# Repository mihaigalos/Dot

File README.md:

# Dot

The Dot is a carrier board designed in Eagle, aimed at gathering sensor data from a variety of sensors and sending them over radio.
Its small design and supply from a coin cell battery make it ideal for deployment anywhere.

Features :
* AtMega328p MCU
* RFM12b / RFM69CW Radio module (pin-compatible)
* On-board ceramic antenna
* CAT24M010TS EEPROM (128kByte)
* AT25SF081 Flash (1MByte)
* Breakout of I2C, SPI and UART-TXD
* Breakout of ADC Pin with pads for on-board divider resistor
* Antenna tuning pads for antenna calibration
* uFL connector for external antenna support 
* Sensors
  * MPU-9250 Movement sensor (9DoF : accelerometers, gyros and magnetometer)
  * TMP102 Temperature and Humidity
  * SI1145 UV Index
  * ISL29125 RGB color
  * Analog light sensor

# License
The Dot is Open Hardware. Use it at your own whim and risk, please share if you find it useful.

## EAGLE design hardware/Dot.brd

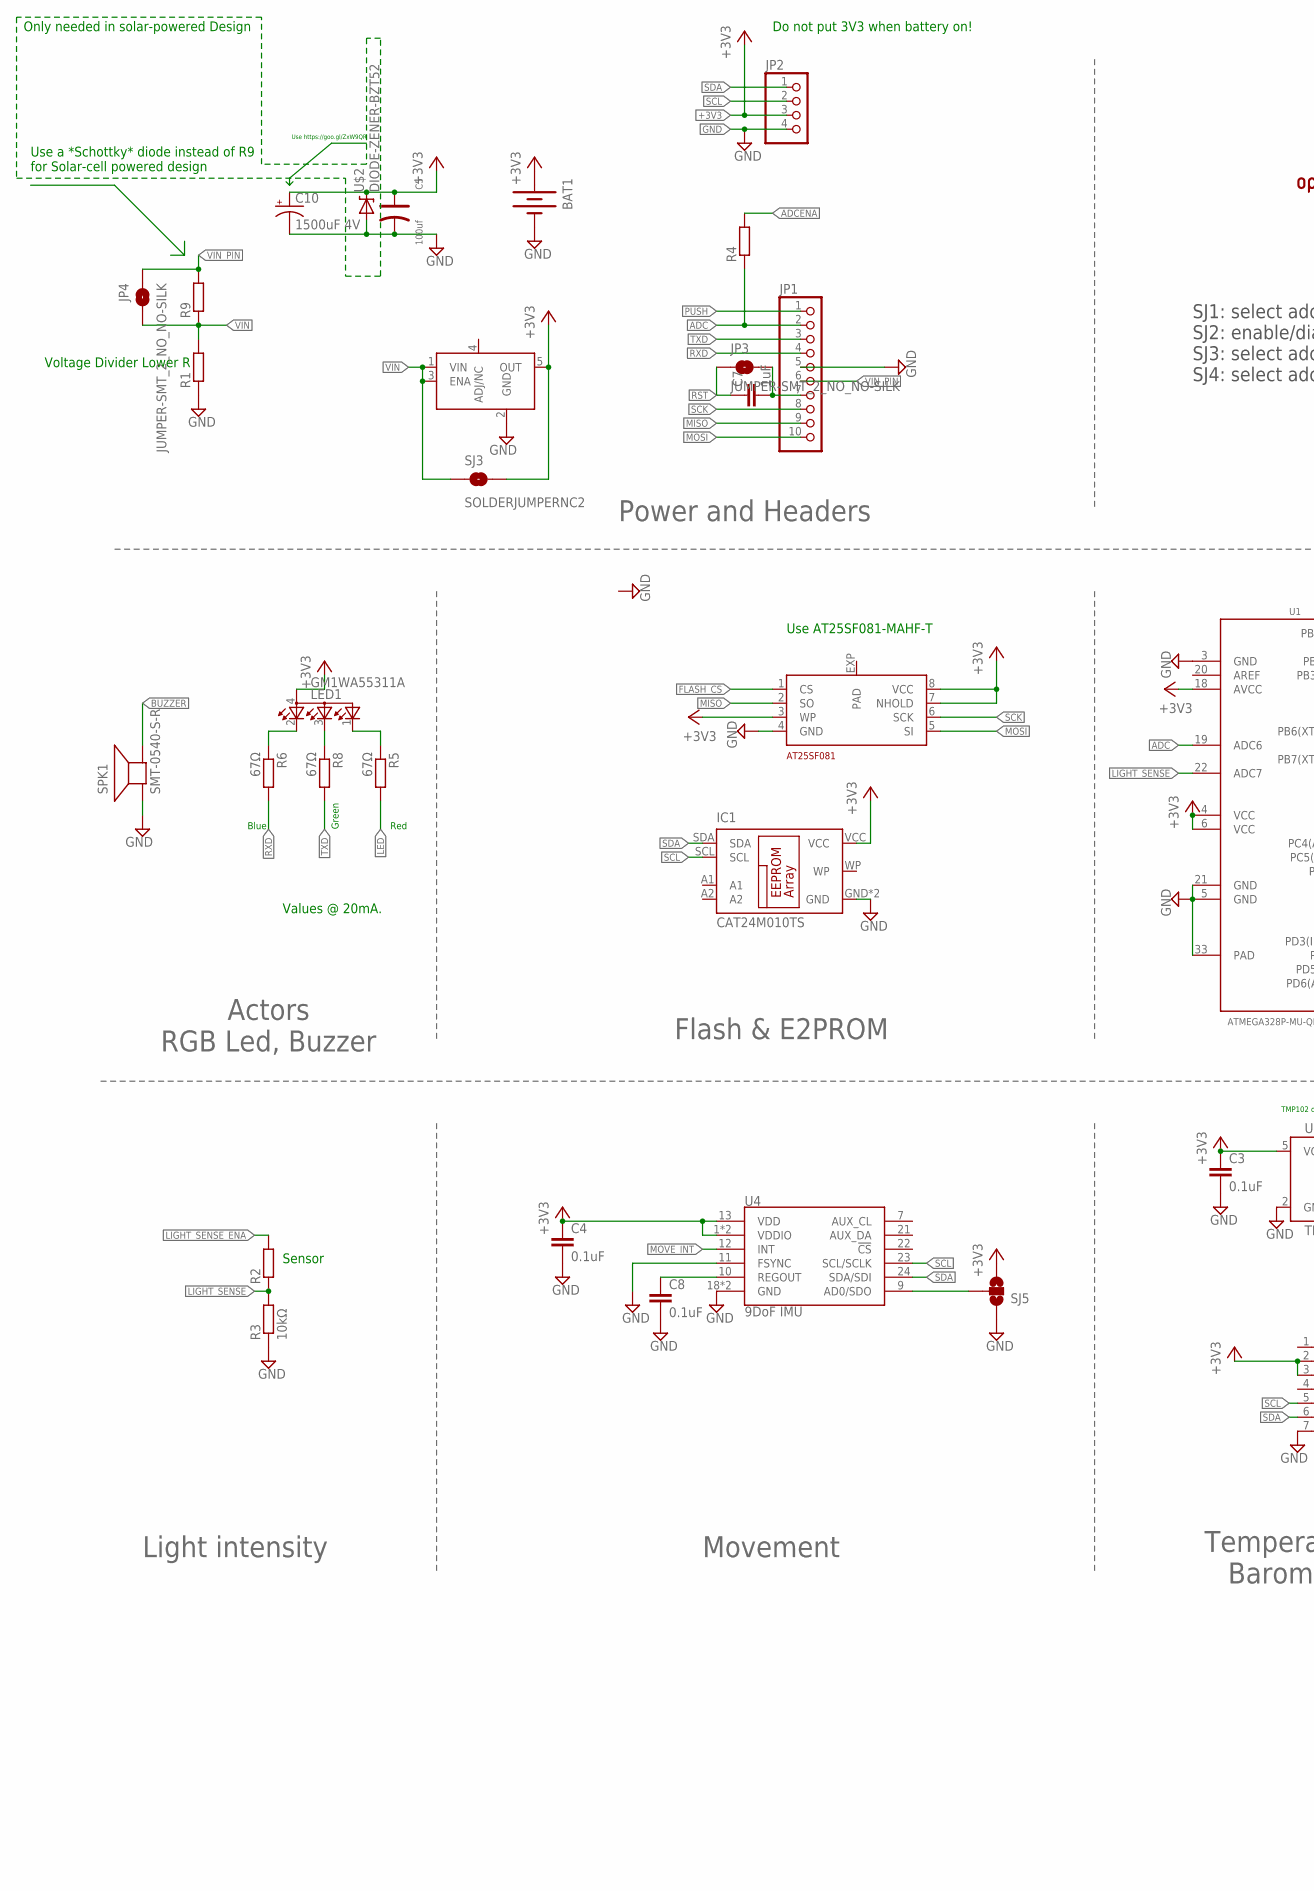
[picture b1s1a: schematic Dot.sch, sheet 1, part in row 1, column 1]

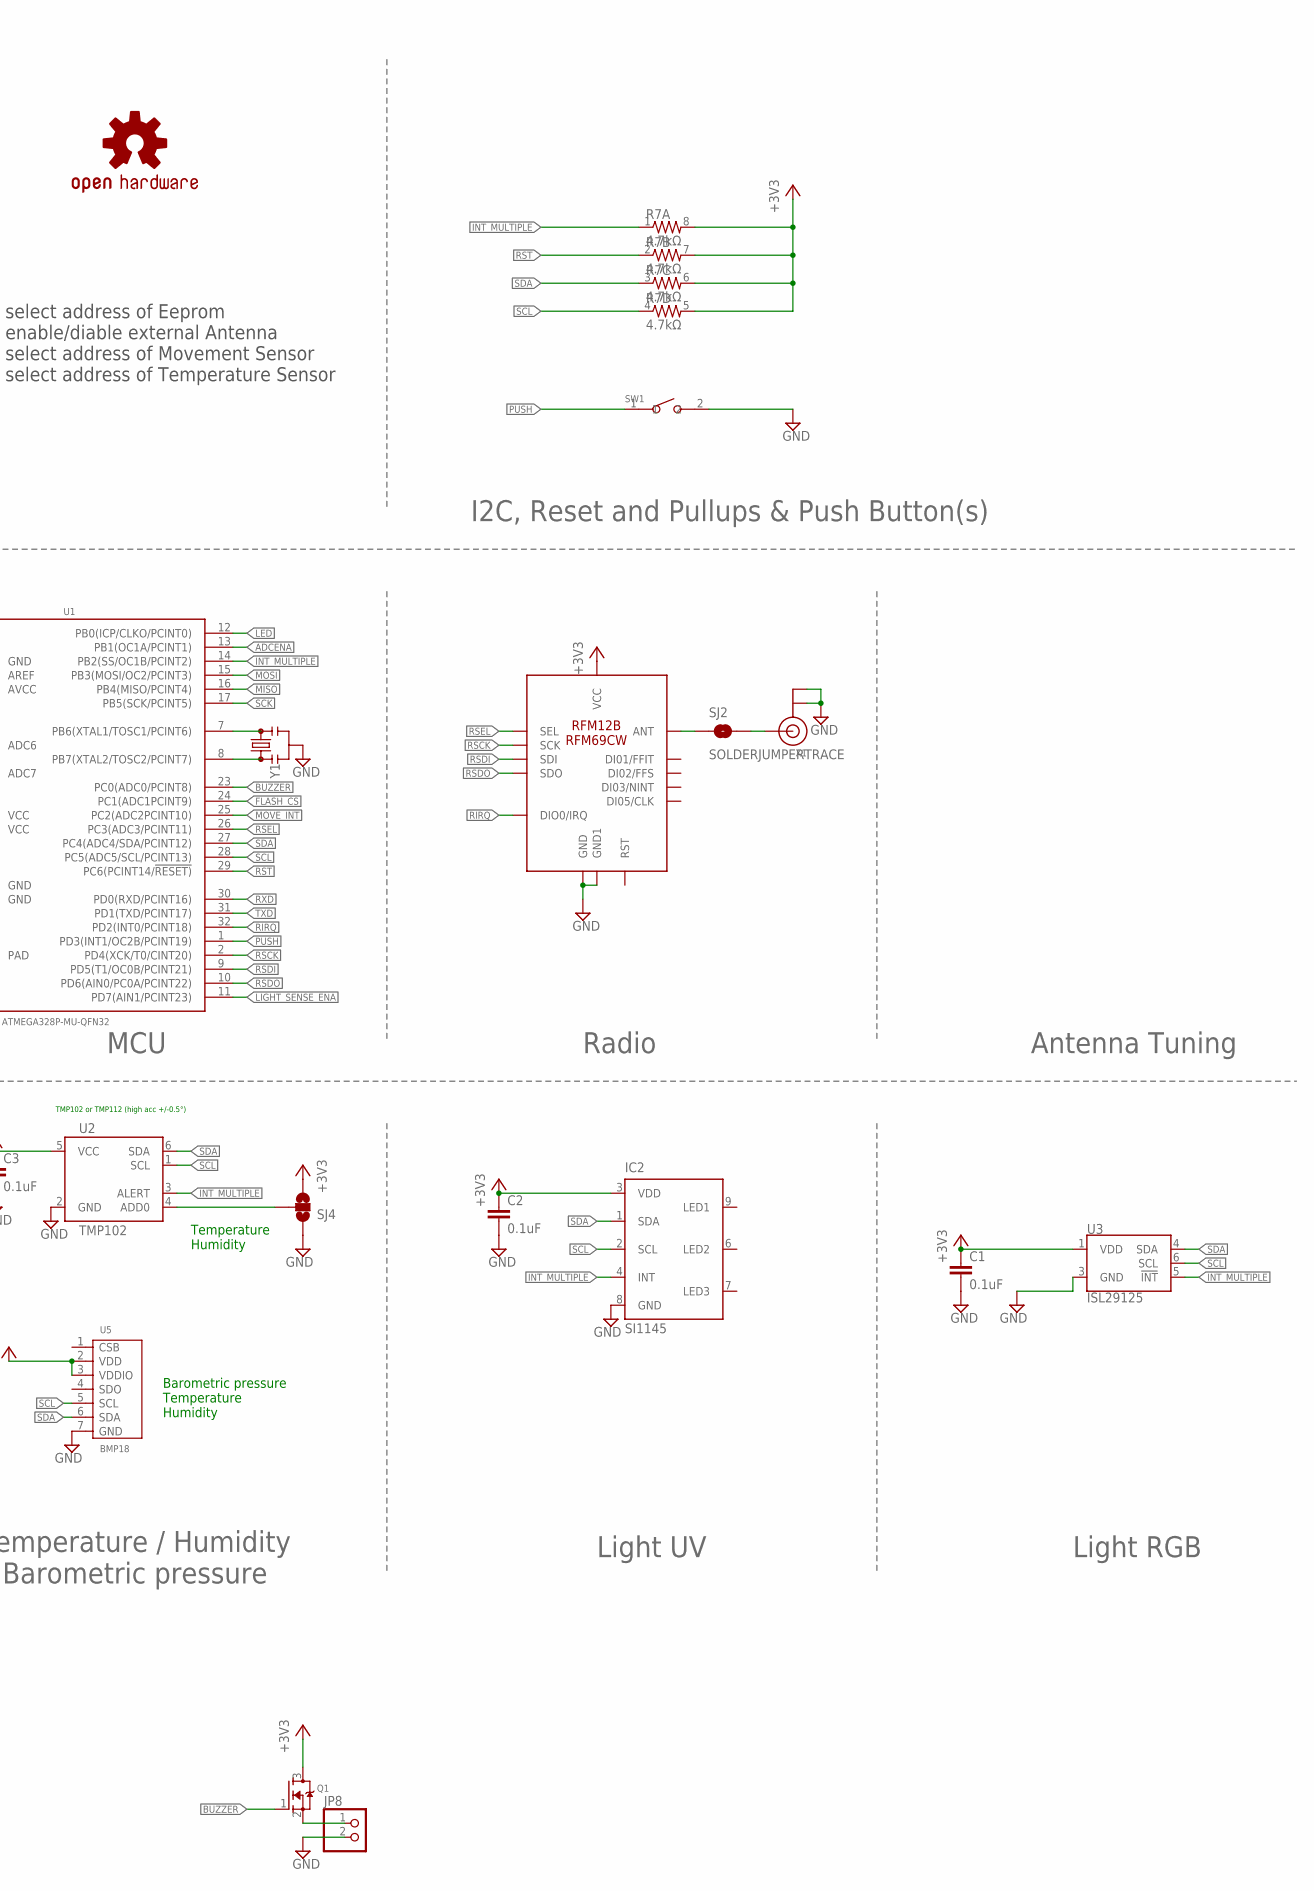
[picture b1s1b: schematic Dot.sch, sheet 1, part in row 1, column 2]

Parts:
BAT1: BATTERY20PTH; BATTCOM_20MM_PTH
C1, C2, C3, C4, C8: 0.1uF; C0603
C5: 100uf; AVX-A
C7: 1uF; C0603
C10: 1500uF 4V; CT7343
IC1: CAT24M010TS; TSSOP8
IC2: SI1145; QFN-10
JP1: PINHD-1X10; 1X10
JP2: PINHD-1X4; 1X04
JP3, JP4: JUMPER-SMT_2_NO_NO-SILK; SMT-JUMPER_2_NO_NO-SILK
JP8: PINHD-1X2; 1X02
LED1: GM1WA55311A
LOGO1: OSHW-LOGOS; OSHW-LOGO-S
Q1: MOSFET-NREFLOW; SOT23
R1, R4, R9: R-EU_R0603; R0603
R2: R-EU_R0805; R0805
R3: 10kΩ; R0603
R5, R6, R8: 67Ω; R0603
R7: 4.7kΩ; 0603-ARV
SJ2: SOLDERJUMPERTRACE; SJ_2S-TRACE
SJ3: SOLDERJUMPERNC2; SJ_2S-NOTRACE
SJ4, SJ5: SOLDERJUMPER_2WAYS; SJ_3
SPK1: SMT-0540-S-R
SW1: SMD-BUTTON(2P-6.0X3.0X2.5MM)-DHT-1163S; SW2-4.0-6.0X3.0X2.5MM
U1: ATMEGA328P-MU-QFN32; QFN32G-0.5-5X5MM
U2: TMP102; SOT563
U3: ISL29125; ODFN-6
U4: 9DoF IMU; QFN24-3X3
U5: BMP18; LGA7-1.5-3.8X3.6MM
U$1: RFM12B/69CW
U$2: DIODE-ZENER-BZT52; SOD-323
U$3: AT25SF081; DFN-2X3
U$4: LDCL015; SOT23-5
X1: ANTENNA_U.FL; U.FL
Y1: RESONATORSMD-3.2X1.3; RESONATOR-SMD-3.2X1.3

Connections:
+3V3: BAT1.1 (+), C1.1, C2.1, C3.1, C4.1, C5.+, C10.+, IC1.VCC, IC2.3 (VDD), JP2.3, LED1.4 (A), Q1.3 (D), R7.5 (2), R7.6 (2), R7.7 (2), R7.8 (2), SJ3.2, SJ4.3, SJ5.3, U1.4 (VCC), U1.6 (VCC), U1.18 (AVCC), U2.5 (VCC), U3.1 (VDD), U4.1 (VDDIO), U4.8 (VDDIO), U4.13 (VDD), U5.2 (VDD), U5.3 (VDDIO), U$1.VDD (VCC), U$2.1 (C), U$3.3 (WP), U$3.7 (NHOLD), U$3.8 (VCC), U$4.5 (OUT)
ADC: JP1.2, R4.1, U1.19 (ADC6)
ADCENA: R4.2, U1.13 (PB1(OC1A/PCINT1))
BUZZER: Q1.1 (G), SPK1.+ (-), U1.23 (PC0(ADC0/PCINT8))
FLASH_CS: U1.24 (PC1(ADC1PCINT9)), U$3.1 (CS)
GND: BAT1.2 (-), C1.2, C2.2, C3.2, C4.2, C5.-, C8.2, C10.-, IC1.GND, IC1.NC (GND), IC2.8 (GND), JP1.5, JP2.4, JP8.2, R1.1, R3.1, SJ4.1, SJ5.1, SPK1.- (+), SW1.2, U1.3 (GND), U1.5 (GND), U1.21 (GND), U1.33 (PAD), U2.2 (GND), U3.3 (GND), U4.11 (FSYNC), U4.18 (GND), U4.20 (GND), U5.7 (GND), U$1.GND, U$1.GND1, U$2.2 (A), U$3.4 (GND), U$4.2 (GND), X1.1 (GND), X1.2 (GND), Y1.2
INT_MULTIPLE: IC2.4 (INT), R7.1, U1.14 (PB2(SS/OC1B/PCINT2)), U2.3 (ALERT), U3.5 (!INT)
LED: R5.2, U1.12 (PB0(ICP/CLKO/PCINT0))
LIGHT_SENSE: R2.1, R3.2, U1.22 (ADC7)
LIGHT_SENSE_ENA: R2.2, U1.11 (PD7(AIN1/PCINT23))
MISO: JP1.9, U1.16 (PB4(MISO/PCINT4)), U$3.2 (SO)
MOSI: JP1.10, U1.15 (PB3(MOSI/OC2/PCINT3)), U$3.5 (SI)
MOVE_INT: U1.25 (PC2(ADC2PCINT10)), U4.12 (INT)
unnamed: LED1.3 (CBLUE), R8.1
unnamed: SJ2.1, U$1.ANT
unnamed: LED1.2 (CRED), R6.1
unnamed: C7.2, JP1.7, JP3.2
unnamed: U1.7 (PB6(XTAL1/TOSC1/PCINT6)), Y1.3
unnamed: SJ2.2, X1.3 (SIGNAL)
unnamed: U1.8 (PB7(XTAL2/TOSC2/PCINT7)), Y1.1
unnamed: SJ4.2, U2.4 (ADD0)
unnamed: C8.1, U4.10 (REGOUT)
unnamed: SJ5.2, U4.9 (AD0/SDO)
unnamed: LED1.1 (CGREEN), R5.1
unnamed: JP8.1, Q1.2 (S)
PUSH: JP1.1, SW1.1, U1.1 (PD3(INT1/OC2B/PCINT19))
RIRQ: U1.32 (PD2(INT0/PCINT18)), U$1.IRQ (DIO0/IRQ)
RSCK: U1.2 (PD4(XCK/T0/CINT20)), U$1.SCK
RSDI: U1.9 (PD5(T1/OC0B/PCINT21)), U$1.SDI
RSDO: U1.10 (PD6(AIN0/PC0A/PCINT22)), U$1.SDO
RSEL: U1.26 (PC3(ADC3/PCINT11)), U$1.SEL
RST: C7.1, JP3.1, R7.2 (1), U1.29 (PC6(PCINT14/!RESET))
RXD: JP1.4, R6.2, U1.30 (PD0(RXD/PCINT16))
SCK: JP1.8, U1.17 (PB5(SCK/PCINT5)), U$3.6 (SCK)
SCL: IC1.SCL, IC2.2 (SCL), JP2.2, R7.4 (1), U1.28 (PC5(ADC5/SCL/PCINT13)), U2.1 (SCL), U3.6 (SCL), U4.23 (SCL/SCLK), U5.5 (SCL)
SDA: IC1.SDA, IC2.1 (SDA), JP2.1, R7.3 (1), U1.27 (PC4(ADC4/SDA/PCINT12)), U2.6 (SDA), U3.4 (SDA), U4.24 (SDA/SDI), U5.6 (SDA)
TXD: JP1.3, R8.2, U1.31 (PD1(TXD/PCINT17))
VIN: JP4.2, R1.2, R9.1, SJ3.1, U$4.1 (VIN), U$4.3 (ENA)
VIN_PIN: JP1.6, JP4.1, R9.2

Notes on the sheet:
Sensor
Do not put 3V3 when battery on!
SJ1: select address of Eeprom SJ2: enable/diable external Antenna SJ3: select address of Movement Sensor SJ4: select address of Temperature Sensor
Movement
Light UV
Light intensity
Flash & E2PROM
MCU
Radio
Light RGB
Actors RGB Led, Buzzer
Antenna Tuning
Power and Headers
I2C, Reset and Pullups & Push Button(s)
Values @ 20mA.
Barometric pressure Temperature Humidity
Temperature / Humidity Barometric pressure
Temperature Humidity
TMP102 or TMP112 (high acc +/-0.5°)
Blue
Green
Red
Voltage Divider Lower R
Use https://goo.gl/ZxW9QR
Use a *Schottky* diode instead of R9 for Solar-cell powered design
Only needed in solar-powered Design
Use AT25SF081-MAHF-T

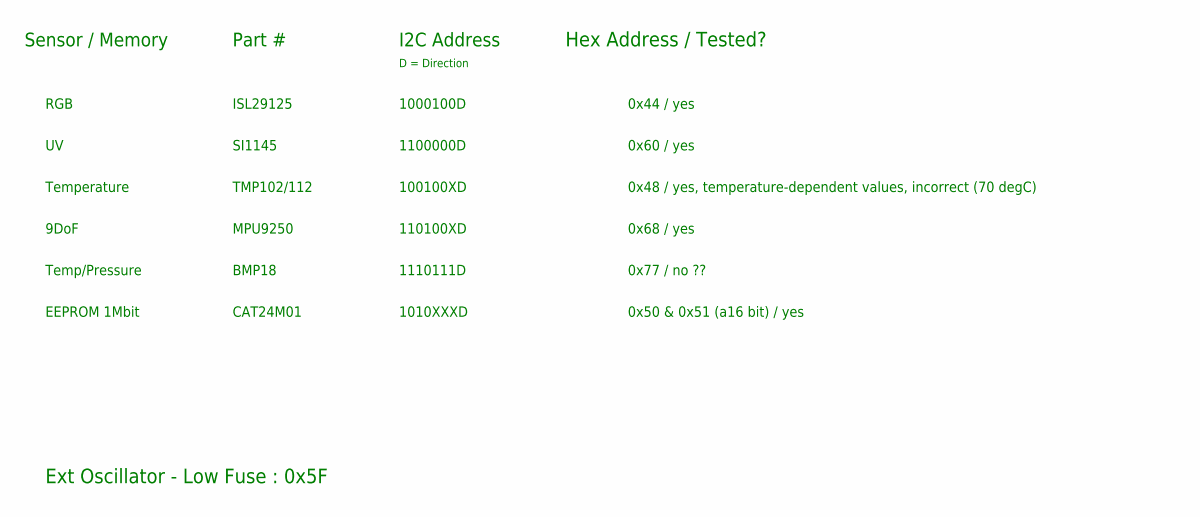
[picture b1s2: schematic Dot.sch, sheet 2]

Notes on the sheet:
Sensor / Memory
Part #
I2C Address
RGB
ISL29125
1000100D
SI1145
1100000D
Temperature
TMP102/112
100100XD
9DoF
MPU9250
110100XD
Hex Address / Tested?
0x44 / yes
0x60 / yes
Temp/Pressure
BMP18
1110111D
0x77 / no ??
0x48 / yes, temperature-dependent values, incorrect (70 degC)
EEPROM 1Mbit
CAT24M01
1010XXXD
0x50 & 0x51 (a16 bit) / yes
D = Direction
0x68 / yes
Ext Oscillator - Low Fuse : 0x5F

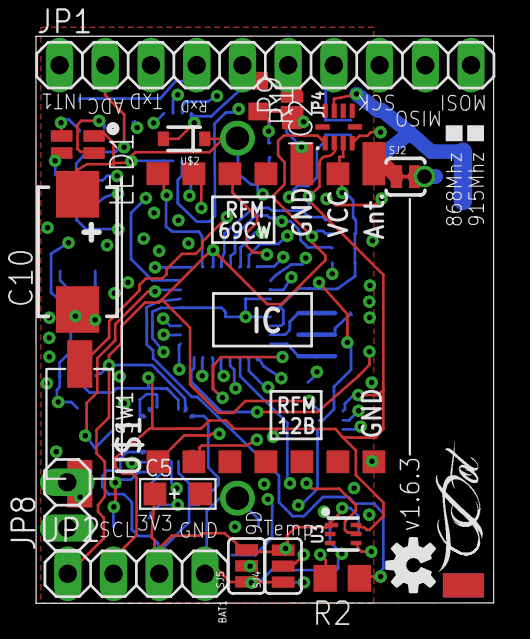
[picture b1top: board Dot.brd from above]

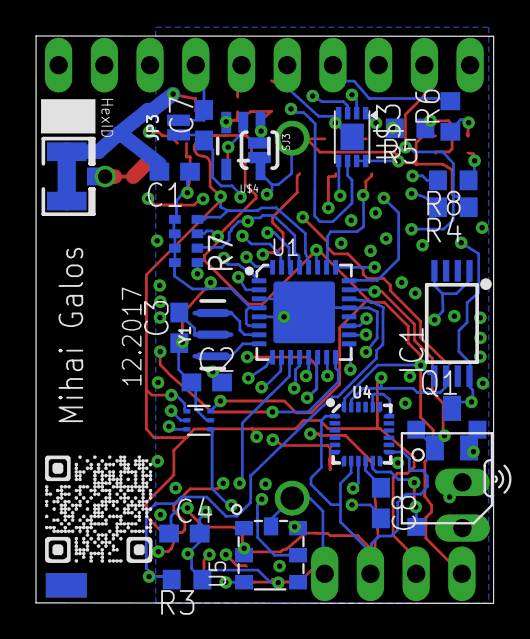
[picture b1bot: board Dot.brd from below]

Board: 4 copper layers, 25.4 x 31.5 mm, 45 parts (25 on the bottom side), 39 nets.

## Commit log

2017-01-22 v0.3
2017-01-22 v0.5
2017-01-22 adding readme
2017-01-22 updating readme
2017-01-22 adding pdf schematic
2017-01-22 udpating schematic
2017-01-22 updating description
2017-06-13 v1.3
2017-06-13 * Corrected RGB Led layout * Added 100uF Cap. Should soften discharges up to 30mA for 1ms. * Cap recharges in 175ms.
2017-06-13 Updating License
2017-06-28 Moving lower 100uF Cap to leave room fo the 3V3 and GND labels.
2017-06-28 Added voltage divider for input voltage measuring.
2017-06-28 Adding solderjumper for bypassing Voltage Regulator
2017-06-28 Removing schematic.pdf since development still ongoing
2017-06-29 Added cap for Reset via DTR pin / Easy Arduino upload
2017-07-09 Add holes for sawing off if necessary
2017-07-09 Update led : G(TxD) B(RxD) R(LED)
2017-07-09 Readd QR, improve labels
2017-07-09 Move QR to avoid vias
2017-07-09 Reorder drills for cut
2017-07-09 Switch to Billy Argel font for Dot and Name words
2017-07-09 Add pullup to UV, RGB and Temp. Their IRQ share same line
2017-07-19 ? Checkpoint
2017-07-19 Add chrystal oscillator, moved C2 and C3
2017-07-19 Move chrystal and C2 down to balance osc l-r length
2017-07-20 Adjust HexId, add 868/915 Mhz silk
2017-07-20 Add C10 1000uF with enough room, move HexID to other side
2017-07-20 Remove C9 100uF add Zenner 3.6V
2017-08-05 Update description : Use a Schottky instead of R9 for solar cell
2017-08-05 Reposition name graphic
2017-08-05 Add solder joint for antenna on bottom
2017-08-05 Add jumper for C7 Reset
2017-08-15 Refactor name logo to simple text
2017-08-15 Shift via to make space for text silk
2017-09-02 Added AT25SF081, fixed labels
2017-09-02 Rearranging files
2017-09-02 Removing superfluous extra MOSI.
2017-09-02 Updated description and gitignore
2017-09-04 Adding pad for soldering end of antenna top/bottom
2017-09-14 Added MOSFET and pins for external on/off
2017-10-15 Moved Miso via away from the 4.7kOhm array, moved graphics further apart

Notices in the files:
parts and their libraries:
SparkFun: Licensing: CC v3.0 Share-Alike You are welcome to use this library for commercial purposes.
Particle-Devices: Licensing: Designed by Particle.
SparkFun-Sensors: Licensing: Creative Commons ShareAlike 4.0 International - https://creativecommons.org/licenses/by-sa/4.0
